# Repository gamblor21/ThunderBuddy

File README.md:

# ThunderBuddy

This small circuitboard uses an AS3935 chip to detect lightning at distances up to 40km away. By default it supports SPI but can be configured for I2C as well.

The board measures around 2cm a side with a small lightning shaped antenna area on top.

The board can be driven in CircuitPython with the [AS3935 driver](https://github.com/gamblor21/CircuitPython_AS3935).

For an example project using the board please see my [Lightning Detector](https://github.com/gamblor21/Lightning-Detector) project.

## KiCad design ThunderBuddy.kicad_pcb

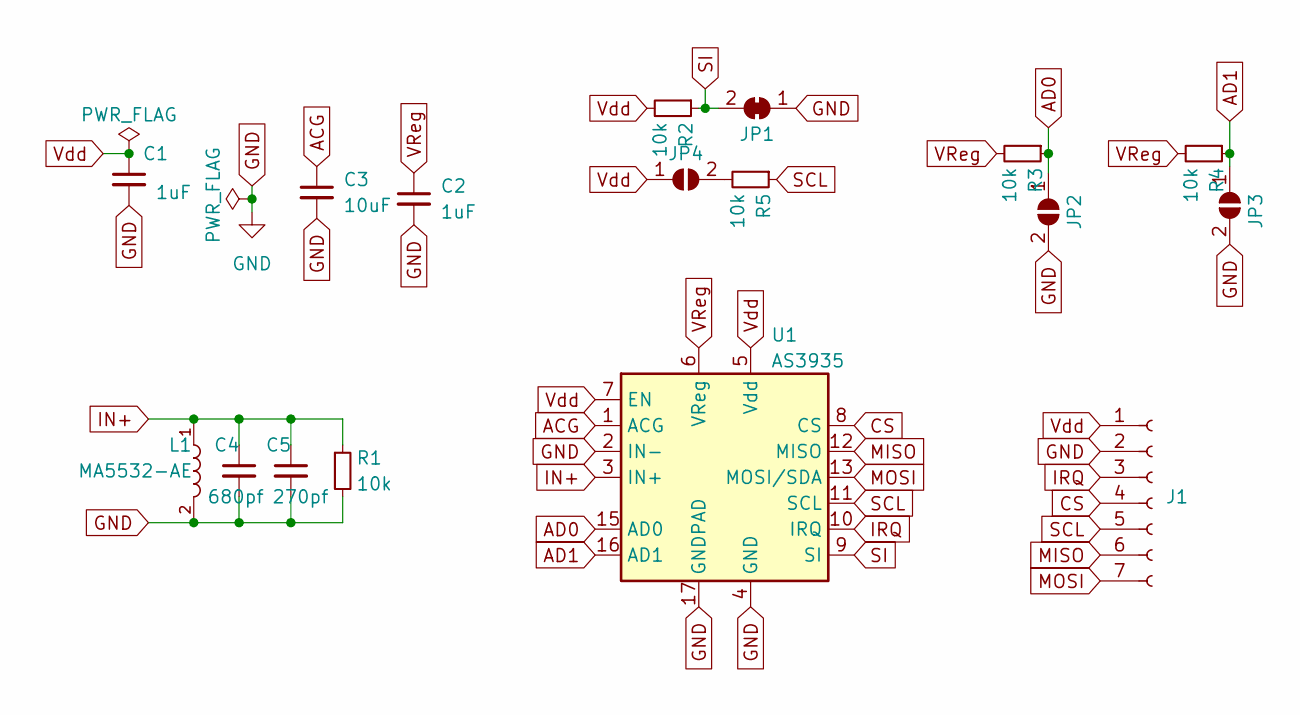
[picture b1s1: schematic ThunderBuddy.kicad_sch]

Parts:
C1, C2: 1uF; C_0805_2012Metric
C3: 10uF; C_0805_2012Metric
C4: 680pf; C_0805_2012Metric
C5: 270pf; C_0805_2012Metric
J1: Headers; PinHeader_1x07_P2.54mm_Vertical
JP1: SI Bridge; SolderJumper-2_P1.3mm_Bridged2Bar_RoundedPad1.0x1.5mm
JP2: AD0 Bridge; SolderJumper-2_P1.3mm_Open_RoundedPad1.0x1.5mm
JP3: AD1 Bridge; SolderJumper-2_P1.3mm_Open_RoundedPad1.0x1.5mm
JP4: SCL Bridge; SolderJumper-2_P1.3mm_Open_RoundedPad1.0x1.5mm
L1: MA5532-AE
R1, R2, R3, R4, R5: 10k; R_0805_2012Metric
U1: AS3935; MLPQ-16-1EP_4x4mm_P0.65mm_EP2.8x2.8mm

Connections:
ACG: C3.1, U1.1 (ACG)
AD0: JP2.1 (A), R3.1, U1.15 (AD0)
AD1: JP3.1 (A), R4.1, U1.16 (AD1)
CS: J1.4, U1.8 (CS)
GND: C1.2, C2.2, C3.2, C4.2, C5.2, J1.2, JP1.1 (A), JP2.2 (B), JP3.2 (B), L1.2, R1.2, U1.2 (IN-), U1.4 (GND), U1.17 (GNDPAD)
IN+: C4.1, C5.1, L1.1, R1.1, U1.3 (IN+)
IRQ: J1.3, U1.10 (IRQ)
MISO: J1.6, U1.12 (MISO)
MOSI: J1.7, U1.13 (MOSI/SDA)
unnamed: JP4.2 (B), R5.2
SCL: J1.5, R5.1, U1.11 (SCL)
SI: JP1.2 (B), R2.1, U1.9 (SI)
VReg: C2.1, R3.2, R4.2, U1.6 (VReg)
Vdd: C1.1, J1.1, JP4.1 (A), R2.2, U1.5 (Vdd), U1.7 (EN)

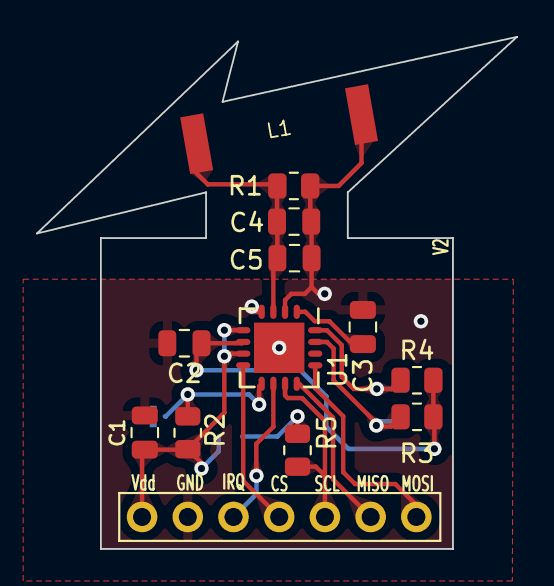
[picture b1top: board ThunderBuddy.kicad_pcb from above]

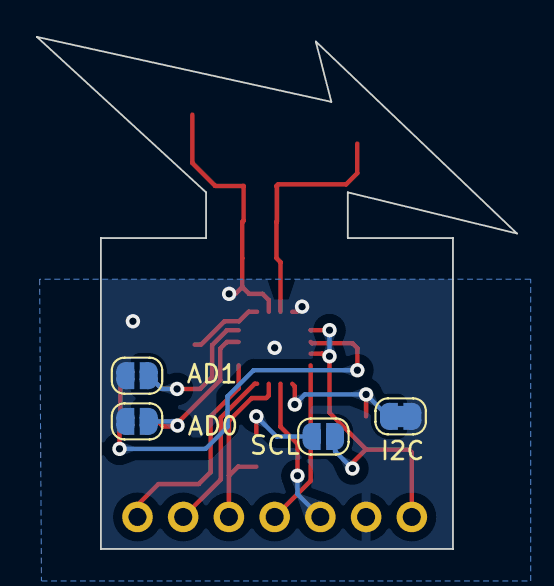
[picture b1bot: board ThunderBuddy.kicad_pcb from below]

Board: 2 copper layers, 26.7 x 28.4 mm, 17 parts (4 on the bottom side), 14 nets.

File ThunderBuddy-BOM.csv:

"Reference","Value","Footprint","Datasheet","PROD_ID","VALUE","Qty"
"C1, C2","1uF","Capacitor_SMD:C_0805_2012Metric","~","","","2"
"C3","10uF","Capacitor_SMD:C_0805_2012Metric","~","","","1"
"C4","680pf","Capacitor_SMD:C_0805_2012Metric","~","","","1"
"C5","270pf","Capacitor_SMD:C_0805_2012Metric","~","","","1"
"J1","Headers","Connector_PinHeader_2.54mm:PinHeader_1x07_P2.54mm_Vertical","~","","","1"
"JP1","SI Bridge","Jumper:SolderJumper-2_P1.3mm_Bridged2Bar_RoundedPad1.0x1.5mm","~","","","1"
"JP2","AD0 Bridge","Jumper:SolderJumper-2_P1.3mm_Open_RoundedPad1.0x1.5mm","~","","","1"
"JP3","AD1 Bridge","Jumper:SolderJumper-2_P1.3mm_Open_RoundedPad1.0x1.5mm","~","","","1"
"JP4","SCL Bridge","Jumper:SolderJumper-2_P1.3mm_Open_RoundedPad1.0x1.5mm","~","","","1"
"L1","MA5532-AE","MA5532:MA5532-AE","","NDUC-11334","100uH","1"
"R1-R5","10k","Resistor_SMD:R_0805_2012Metric","~","","","5"
"U1","AS3935","Package_DFN_QFN:MLPQ-16-1EP_4x4mm_P0.65mm_EP2.8x2.8mm","https://www.embeddedadventures.com/datasheets/AS3935_Datashe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","","","1"

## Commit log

2023-09-20 Version 1
2023-09-20 Version 2
2023-09-20 Rename LICENSE to Software-LICENSE
2023-09-20 Rename hardware-LICENSE.XSCORE to Hardware-LICENSE
